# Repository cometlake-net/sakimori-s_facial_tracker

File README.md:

## License

This hardware design project (including schematics, PCB layout, and routing) is released under the **MIT License**. See the `LICENSE` file for details.

### Third-Party Assets / Acknowledgements

Some component libraries (schematic symbols, footprints, and 3D models) used in this project are provided by [SnapMagic](https://www.snapmagic.com/) (formerly SnapEDA). These specific asset files are licensed under the **Creative Commons Attribution-ShareAlike 4.0 International (CC-BY-SA 4.0)**. 
Please refer to their terms of service for further redistribution or modification of these library files.

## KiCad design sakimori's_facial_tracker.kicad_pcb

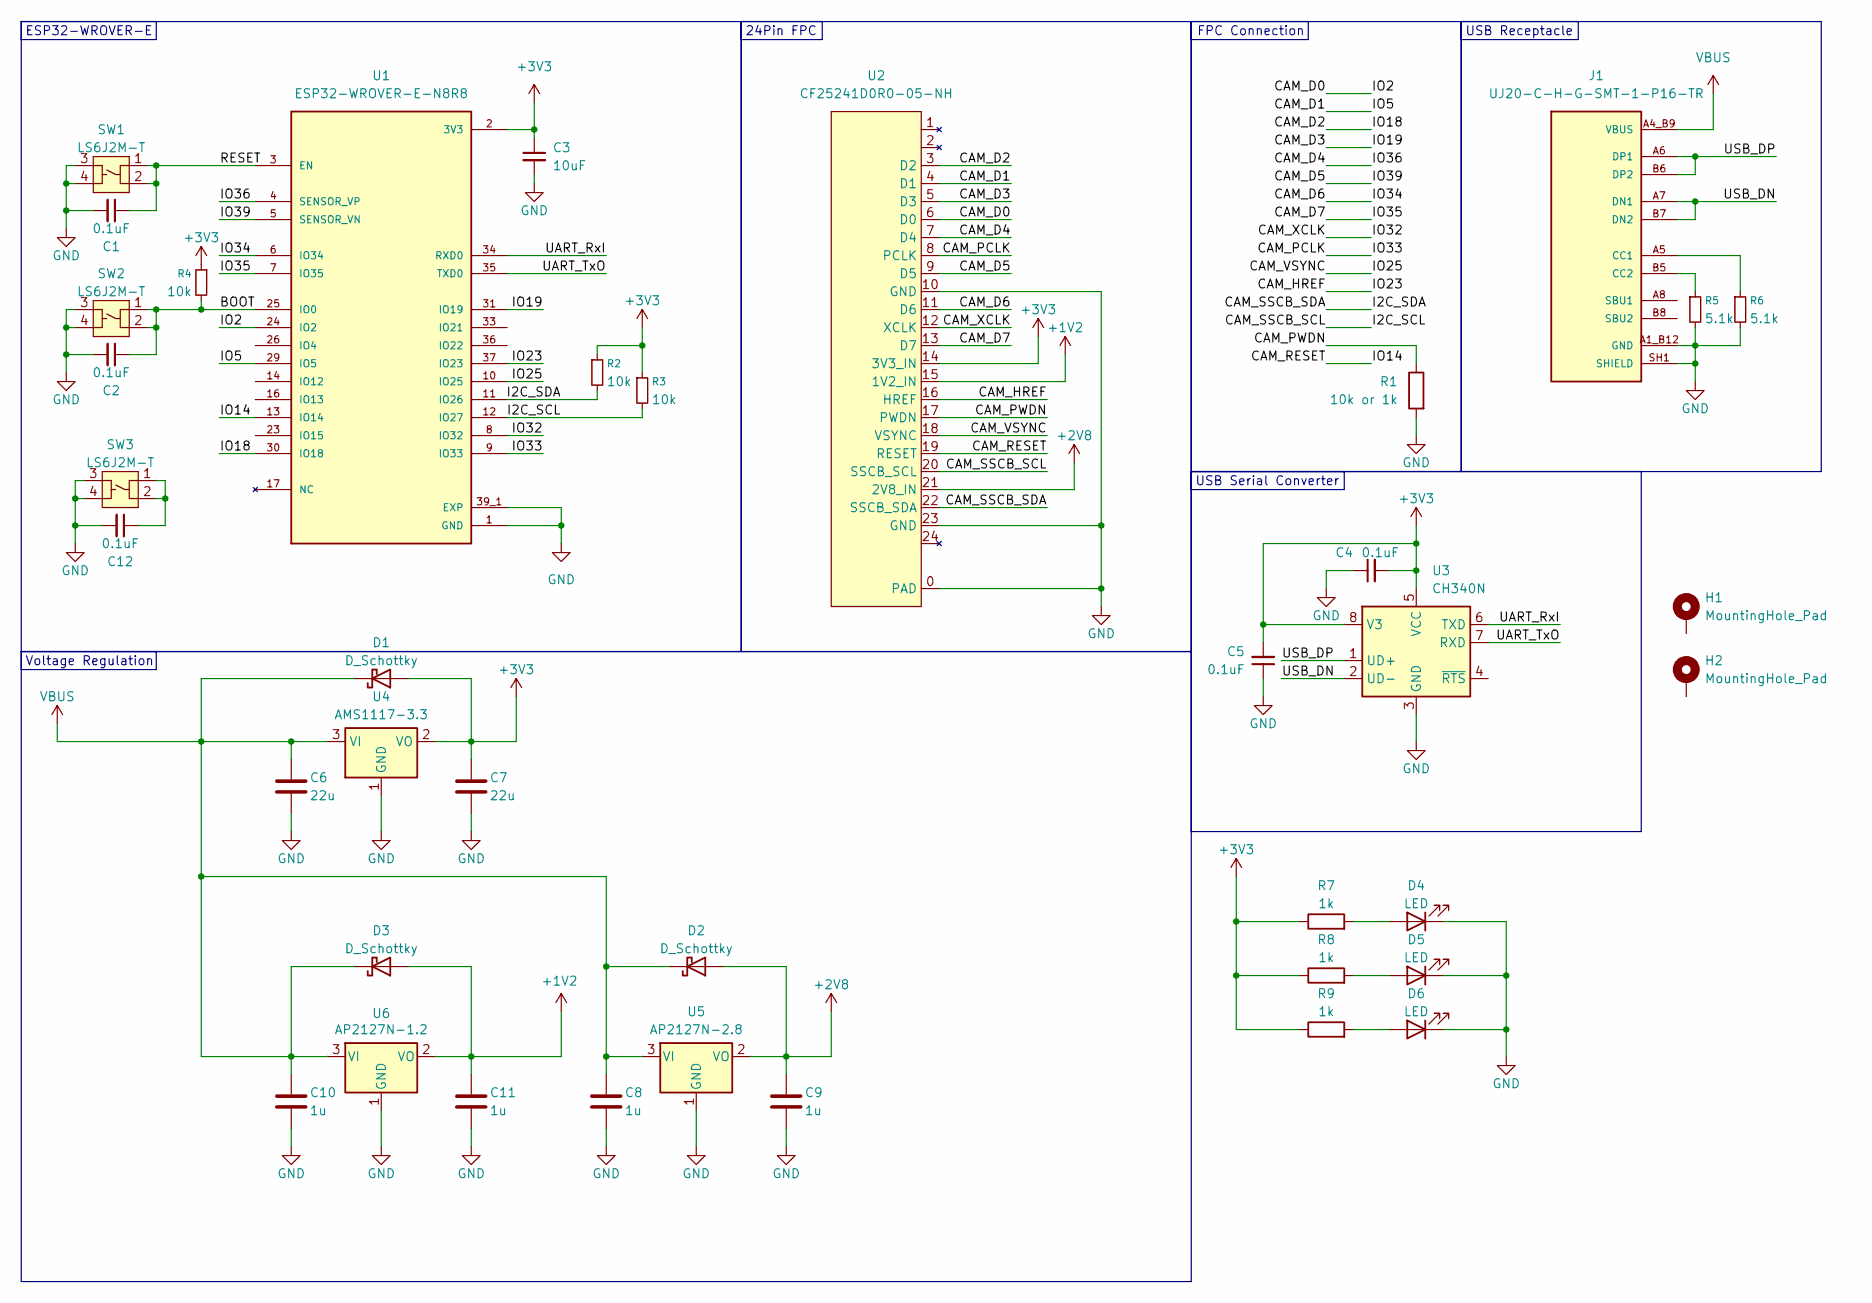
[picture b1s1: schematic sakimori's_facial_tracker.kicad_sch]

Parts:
C1, C2, C4, C5, C12: 0.1uF; C_0603_1608Metric
C3: 10uF; C_0603_1608Metric
C6, C7: 22u; C_0805_2012Metric
C8, C9, C10, C11: 1u; C_0603_1608Metric
D1, D2, D3: D_Schottky; D_SOD-123
D4, D5: LED; LED_1206_3216Metric
D6: LED; LED_0603_1608Metric
H1, H2: MountingHole_Pad; MountingHole_2.2mm_M2_Pad_TopBottom
J1: UJ20-C-H-G-SMT-1-P16-TR; SAMESKY_UJ20-C-H-G-SMT-1-P16-TR; PARTREV 1.0
R1: 10k or 1k; R_0603_1608Metric
R2, R3, R4: 10k; R_0603_1608Metric
R5, R6: 5.1k; R_0603_1608Metric
R7, R8, R9: 1k; R_0603_1608Metric
SW1, SW2, SW3: LS6J2M-T
U1: ESP32-WROVER-E-N8R8; PARTREV 1.6
U2: CF25241D0R0-05-NH
U3: CH340N; JEITA_SOIC-8_3.9x4.9mm_P1.27mm
U4: AMS1117-3.3; SOT-223-3_TabPin2
U5: AP2127N-2.8; SOT-23
U6: AP2127N-1.2; SOT-23

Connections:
+1V2: C11.1, D3.2 (A), U2.15 (1V2_IN), U6.2 (VO)
+2V8: C9.1, D2.2 (A), U2.21 (2V8_IN), U5.2 (VO)
+3V3: C3.1, C4.2, C5.2, C7.1, D1.2 (A), R2.1, R3.1, R4.1, R7.1, R8.1, R9.1, U1.2 (3V3), U2.14 (3V3_IN), U3.5 (VCC), U3.8 (V3), U4.2 (VO)
/BOOT: C2.1, R4.2, SW2.1, SW2.2, U1.25 (IO0)
/CAM_D0: U1.24 (IO2), U2.6 (D0)
/CAM_D1: U1.29 (IO5), U2.4 (D1)
/CAM_D2: U1.30 (IO18), U2.3 (D2)
/CAM_D3: U1.31 (IO19), U2.5 (D3)
/CAM_D4: U1.4 (SENSOR_VP), U2.7 (D4)
/CAM_D5: U1.5 (SENSOR_VN), U2.9 (D5)
/CAM_D6: U1.6 (IO34), U2.11 (D6)
/CAM_D7: U1.7 (IO35), U2.13 (D7)
/CAM_HREF: U1.37 (IO23), U2.16 (HREF)
/CAM_PCLK: U1.9 (IO33), U2.8 (PCLK)
/CAM_PWDN: R1.1, U2.17 (PWDN)
/CAM_RESET: U1.13 (IO14), U2.19 (RESET)
/CAM_SSCB_SCL: R3.2, U1.12 (IO27), U2.20 (SSCB_SCL)
/CAM_SSCB_SDA: R2.2, U1.11 (IO26), U2.22 (SSCB_SDA)
/CAM_VSYNC: U1.10 (IO25), U2.18 (VSYNC)
/CAM_XCLK: U1.8 (IO32), U2.12 (XCLK)
/RESET: C1.1, SW1.1, SW1.2, U1.3 (EN)
/UART_RxI: U1.34 (RXD0), U3.6 (TXD)
/UART_TxO: U1.35 (TXD0), U3.7 (RXD)
/USB_DN: J1.A7 (DN1), J1.B7 (DN2), U3.2 (UD-)
/USB_DP: J1.A6 (DP1), J1.B6 (DP2), U3.1 (UD+)
GND: C1.2, C2.2, C3.2, C4.1, C5.1, C6.2, C7.2, C8.2, C9.2, C10.2, C11.2, C12.2, D4.1 (K), D5.1 (K), D6.1 (K), J1.A1_B12 (GND), J1.B1_A12 (GND), J1.SH1 (SHIELD), J1.SH2 (SHIELD), J1.SH3 (SHIELD), J1.SH4 (SHIELD), R1.2, R5.2, R6.2, SW1.3, SW1.4, SW2.3, SW2.4, SW3.3, SW3.4, U1.1 (GND), U1.15 (GND), U1.38 (GND), U1.39_1 (EXP), U1.39_2 (EXP), U1.39_3 (EXP), U1.39_4 (EXP), U1.39_5 (EXP), U1.39_6 (EXP), U1.39_7 (EXP), U1.39_8 (EXP), U1.39_9 (EXP), U2.0 (PAD), U2.10 (GND), U2.23 (GND), U3.3 (GND), U4.1 (GND), U5.1 (GND), U6.1 (GND)
unnamed: C12.1, SW3.1, SW3.2
unnamed: D4.2 (A), R7.2
unnamed: D5.2 (A), R8.2
unnamed: D6.2 (A), R9.2
unnamed: J1.A5 (CC1), R6.1
unnamed: J1.B5 (CC2), R5.1
VBUS: C6.1, C8.1, C10.1, D1.1 (K), D2.1 (K), D3.1 (K), J1.A4_B9 (VBUS), J1.B4_A9 (VBUS), U4.3 (VI), U5.3 (VI), U6.3 (VI)

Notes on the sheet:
Voltage Regulation
24Pin FPC
USB Serial Converter
FPC Connection
USB Receptacle
ESP32-WROVER-E

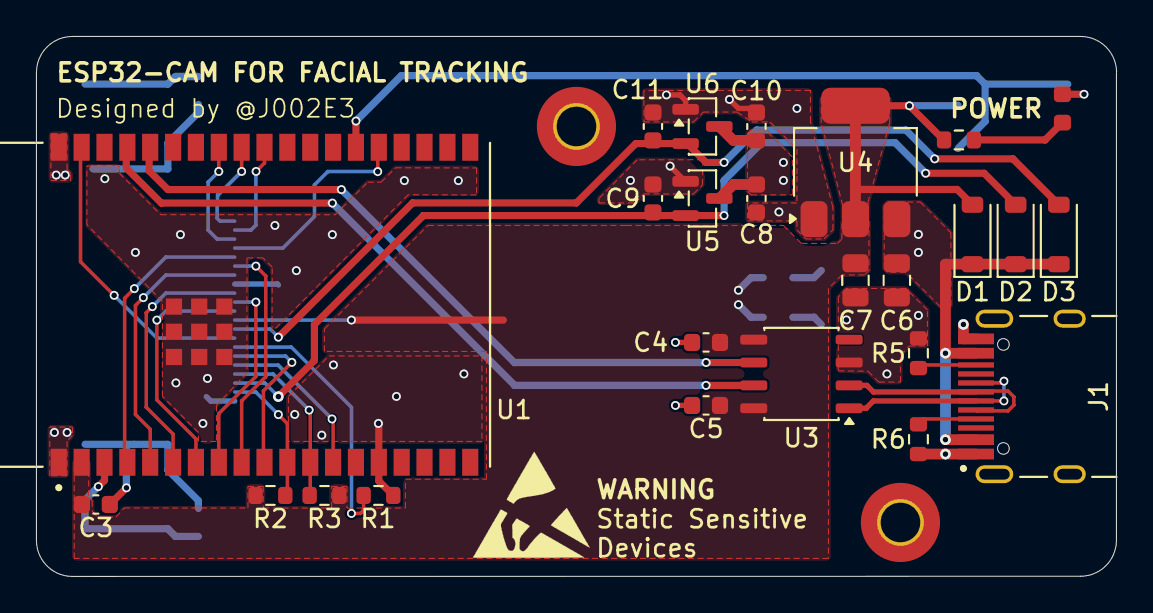
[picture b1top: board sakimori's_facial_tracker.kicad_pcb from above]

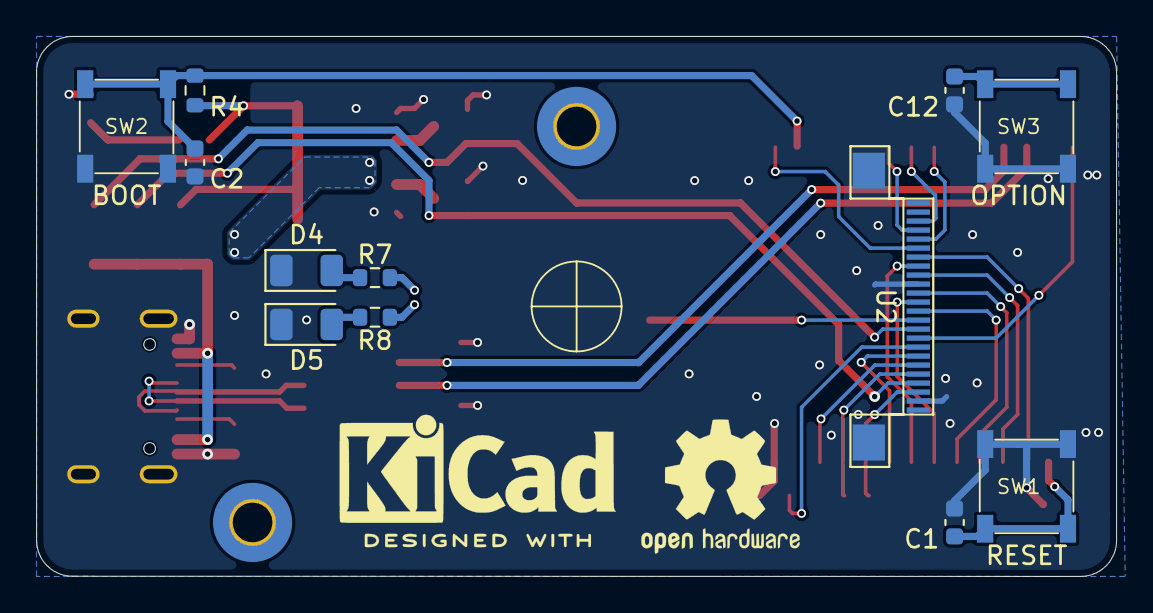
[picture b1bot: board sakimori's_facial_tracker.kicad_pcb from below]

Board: 2 copper layers, 60.0 x 30.0 mm, 39 parts (12 on the bottom side), 33 nets.

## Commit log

2026-04-21 Add MIT License to the project
2026-04-21 Add license and third-party acknowledgements to README
    Added license information and acknowledgements for third-party assets.
